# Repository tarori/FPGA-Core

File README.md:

# FPGA Core Board

* Artix-7 XC7A35T-2FTG256C
* USB Bus Powered
* 80 I/O from Mezzanine Connectors
* On-Board JTAG and 300Mbps FIFO by FT2232H
* 256Mbit Hyper-RAM

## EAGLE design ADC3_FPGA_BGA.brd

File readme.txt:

All vias with 0.3mm drill diameter should be filled and capped.

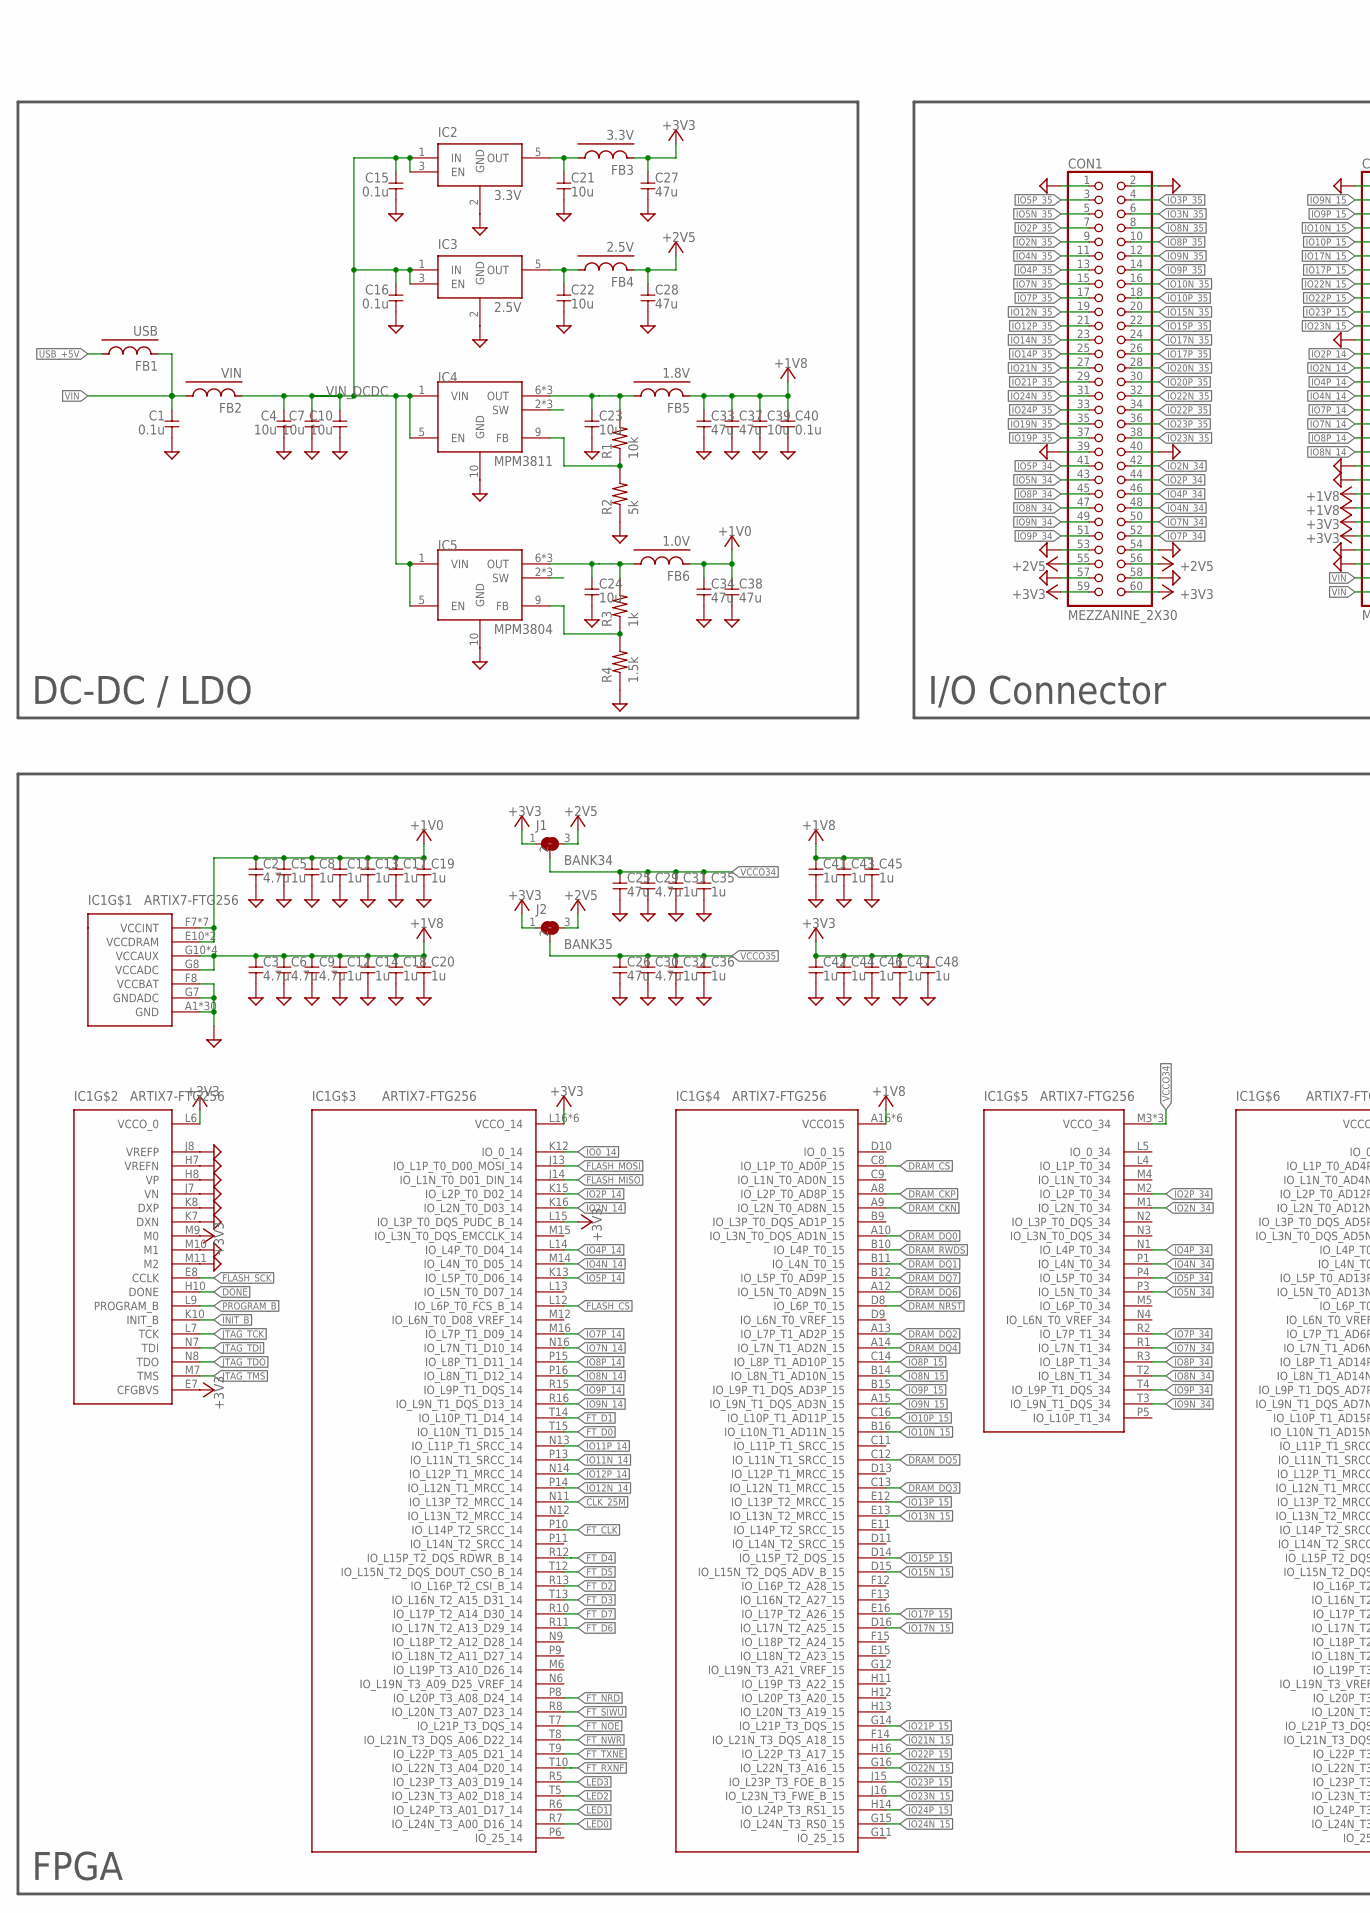
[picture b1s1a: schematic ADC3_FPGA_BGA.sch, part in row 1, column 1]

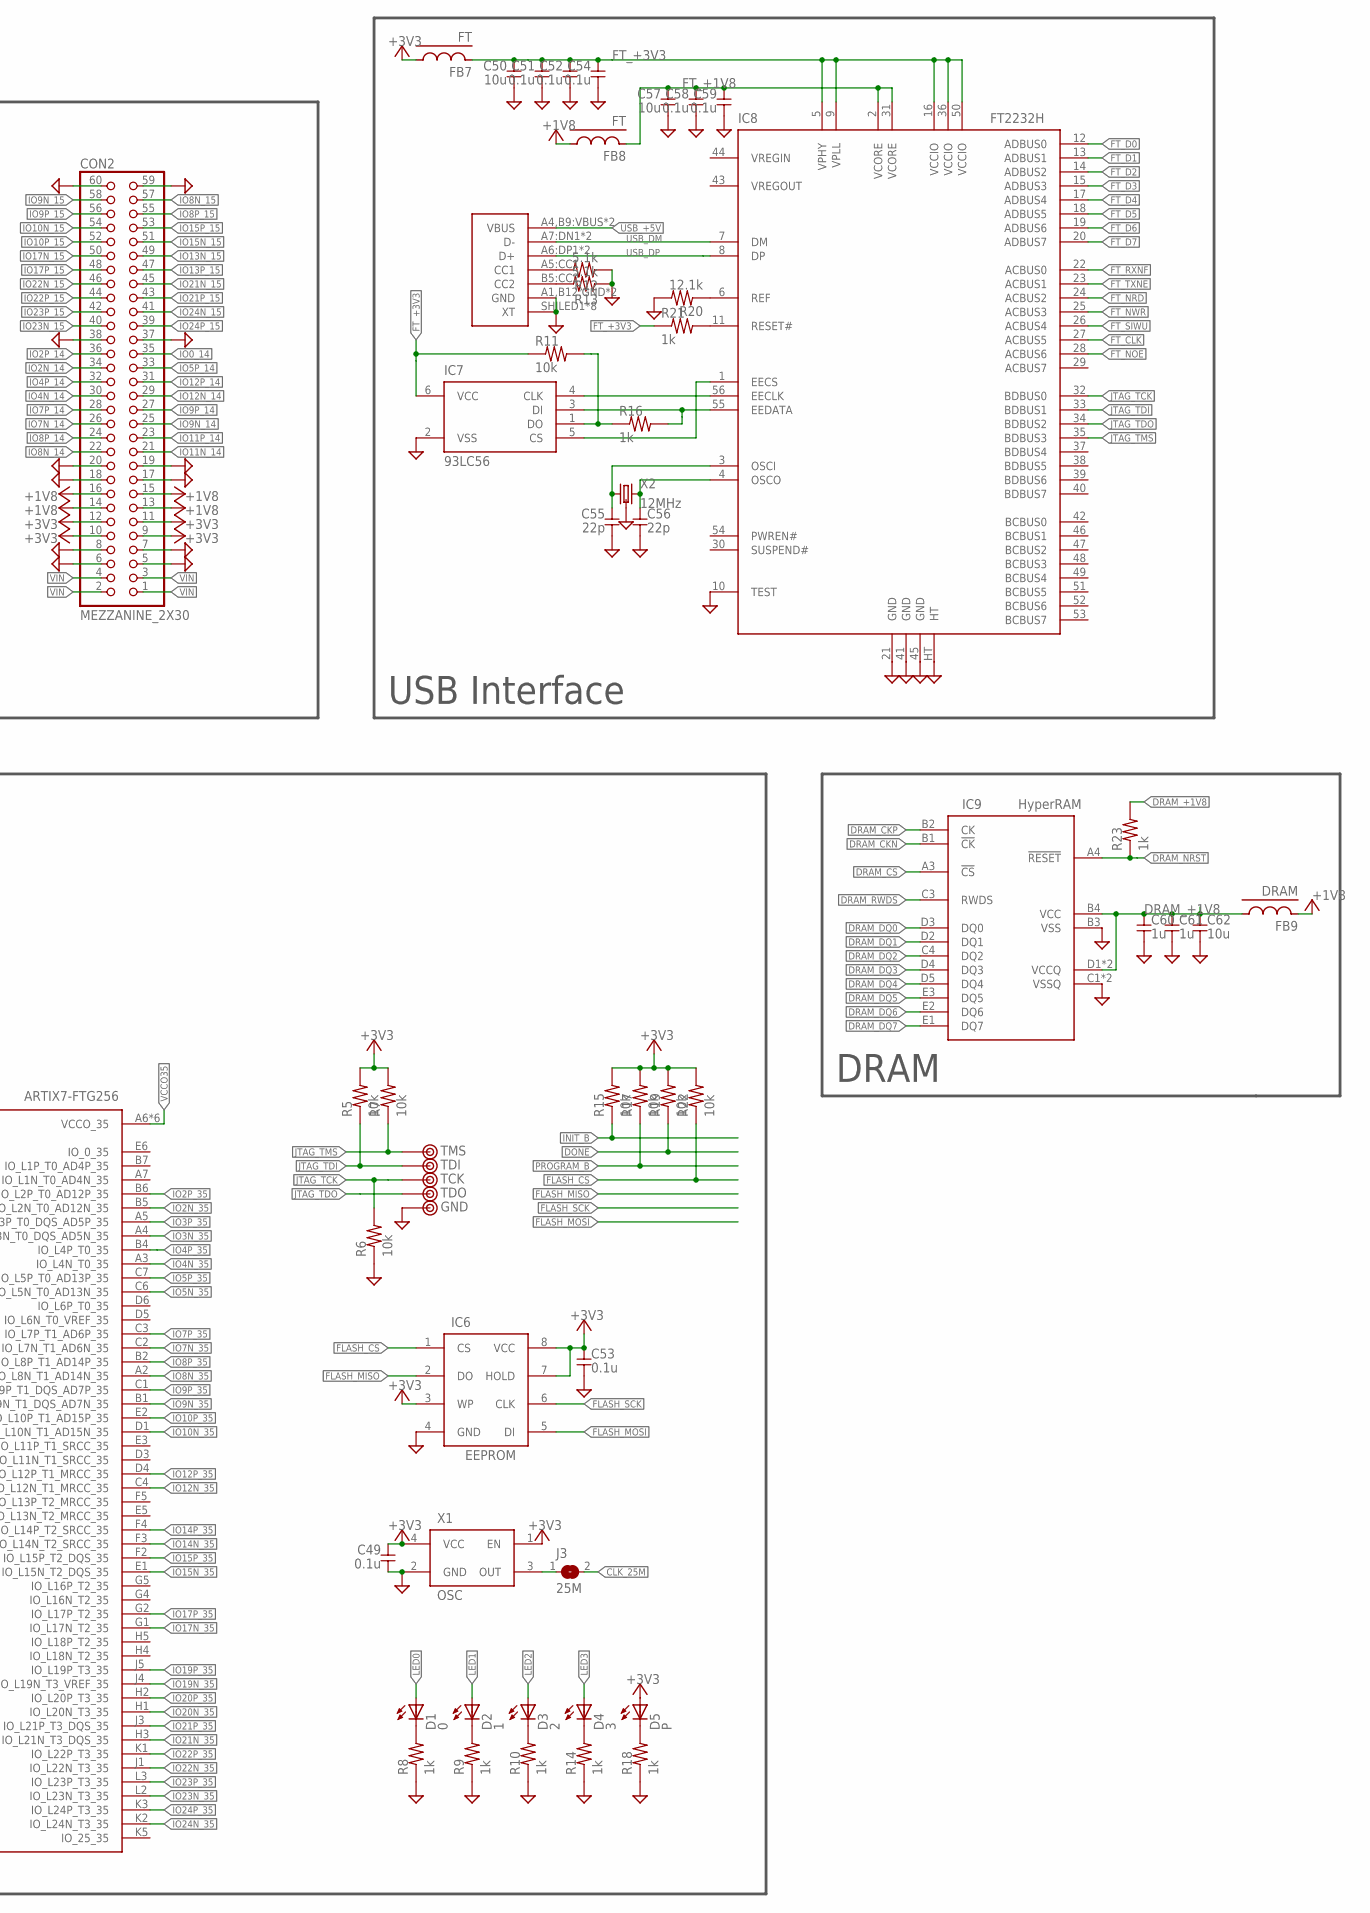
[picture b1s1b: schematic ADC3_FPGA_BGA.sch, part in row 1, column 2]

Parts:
C1, C15, C16, C40, C49, C51, C52, C53, C54, C58, C59: 0.1u; 1608C
C2, C3, C6, C9, C29, C30: 4.7u; 1608C
C4, C62: 10u; 2012
C5, C8, C11, C12, C13, C14, C17, C18, C19, C20, C31, C32, C35, C36, C41, C42, C43, C44, C45, C46, C47, C48: 1u; 1005
C7, C10, C21, C22, C23, C24, C50, C57: 10u; 1608C
C25, C26, C27, C28, C33, C34, C37, C38: 47u; 2012
C39: 10u; 3216
C55, C56: 22p; 1608C
C60, C61: 1u; 1608C
CON1, CON2: MEZZANINE_2X30; MEZZANINE_0.8MM_2X30
CON3: USB-C; 5077CR-16-SMC2-BK-TR
D1: 0; D1608
D2: 1; D1608
D3: 2; D1608
D4: 3; D1608
D5: P; D1608
FB1: USB; 1608-J
FB2: VIN; 1608-J
FB3: 3.3V; 1608-J
FB4: 2.5V; 1608-J
FB5: 1.8V; 1608-J
FB6: 1.0V; 1608-J
FB7, FB8: FT; 1608-J
FB9: DRAM; 1608-J
IC1: ARTIX7-FTG256; FTG256
IC2: 3.3V; SOT23-5
IC3: 2.5V; SOT23-5
IC4: MPM3811; QFN-10
IC5: MPM3804; QFN-10
IC6: EEPROM; SOIC-SOIJ-8
IC7: 93LC56; SOT23-6
IC8: FT2232H; QFN56-HT
IC9: HyperRAM; TFBGA24
J1: BANK34; 1608-3-J
J2: BANK35; 1608-3-J
J3: 25M; 1608-J
R1, R5, R6, R7, R11, R15, R17, R19, R22: 10k; 1608
R2: 5k; 1608
R3, R8, R9, R10, R14, R16, R18, R21, R23: 1k; 1608
R4: 1.5k; 1608
R12, R13: 5.1k; 1608
R20: 12.1k; 1608
TP1: TMS; TESTPAD-SMALL
TP2: TDI; TESTPAD-SMALL
TP3: TCK; TESTPAD-SMALL
TP4: TDO; TESTPAD-SMALL
TP5: GND; TESTPAD-SMALL
X1: OSC; KC3225
X2: 12MHz; KC3225

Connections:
1.0V_DCDC_SW: IC5.2 (SW), IC5.3 (SW), IC5.4 (SW)
1.8V_DCDC_SW: IC4.2 (SW), IC4.3 (SW), IC4.4 (SW)
+1V0: C2.1, C5.1, C8.1, C11.1, C13.1, C17.1, C19.1, C34.1, C38.1, FB6.2, IC1.E10 (VCCDRAM), IC1.F7 (VCCINT), IC1.F9 (VCCINT), IC1.F11 (VCCDRAM), IC1.G6 (VCCINT), IC1.H9 (VCCINT), IC1.J6 (VCCINT), IC1.K9 (VCCINT), IC1.L8 (VCCINT)
+1V0_DCDC: C24.1, FB6.1, IC5.6 (OUT), IC5.7 (OUT), IC5.8 (OUT), R3.2
+1V0_DCDC_FB: IC5.9 (FB), R3.1, R4.2
+1V8: C3.1, C6.1, C9.1, C12.1, C14.1, C18.1, C20.1, C33.1, C37.1, C39.1, C40.1, C41.1, C43.1, C45.1, CON2.13, CON2.14, CON2.15, CON2.16, FB5.2, FB8.1, FB9.2, IC1.A16 (VCCO15), IC1.B13 (VCCO15), IC1.C10 (VCCO15), IC1.E14 (VCCO15), IC1.G8 (VCCADC), IC1.G10 (VCCAUX), IC1.H15 (VCCO15), IC1.J10 (VCCAUX), IC1.J12 (VCCO15), IC1.K11 (VCCAUX), IC1.L10 (VCCAUX)
+1V8_DCDC: C23.1, FB5.1, IC4.6 (OUT), IC4.7 (OUT), IC4.8 (OUT), R1.2
+1V8_DCDC_FB: IC4.9 (FB), R1.1, R2.2
+2V5: C28.1, CON1.55, CON1.56, FB4.2, J1.3, J2.3
+2V5_LDO: C22.1, FB4.1, IC3.5 (OUT)
+3V3: C27.1, C42.1, C44.1, C46.1, C47.1, C48.1, C49.1, C53.1, CON1.59, CON1.60, CON2.9, CON2.10, CON2.11, CON2.12, D5.A, FB3.2, FB7.1, IC1.E7 (CFGBVS), IC1.L6 (VCCO_0), IC1.L15 (IO_L3P_T0_DQS_PUDC_B_14), IC1.L16 (VCCO_14), IC1.M9 (M0), IC1.M13 (VCCO_14), IC1.N10 (VCCO_14), IC1.P7 (VCCO_14), IC1.R14 (VCCO_14), IC1.T11 (VCCO_14), IC6.3 (WP), IC6.7 (HOLD), IC6.8 (VCC), J1.1, J2.1, R5.2, R7.2, R15.2, R17.2, R19.2, R22.2, X1.1 (EN), X1.4 (VCC)
+3V3_LDO: C21.1, FB3.1, IC2.5 (OUT)
CLK_25M: IC1.N11 (IO_L13P_T2_MRCC_14), J3.2
DONE: IC1.H10 (DONE), R19.1
DRAM_+1V8: C60.1, C61.1, C62.1, FB9.1, IC9.B4 (VCC), IC9.D1 (VCCQ), IC9.E4 (VCCQ), R23.2
DRAM_CKN: IC1.A9 (IO_L2N_T0_AD8N_15), IC9.B1 (!CK)
DRAM_CKP: IC1.A8 (IO_L2P_T0_AD8P_15), IC9.B2 (CK)
DRAM_CS: IC1.C8 (IO_L1P_T0_AD0P_15), IC9.A3 (!CS)
DRAM_DQ0: IC1.A10 (IO_L3N_T0_DQS_AD1N_15), IC9.D3 (DQ0)
DRAM_DQ1: IC1.B11 (IO_L4N_T0_15), IC9.D2 (DQ1)
DRAM_DQ2: IC1.A13 (IO_L7P_T1_AD2P_15), IC9.C4 (DQ2)
DRAM_DQ3: IC1.C13 (IO_L12N_T1_MRCC_15), IC9.D4 (DQ3)
DRAM_DQ4: IC1.A14 (IO_L7N_T1_AD2N_15), IC9.D5 (DQ4)
DRAM_DQ5: IC1.C12 (IO_L11N_T1_SRCC_15), IC9.E3 (DQ5)
DRAM_DQ6: IC1.A12 (IO_L5N_T0_AD9N_15), IC9.E2 (DQ6)
DRAM_DQ7: IC1.B12 (IO_L5P_T0_AD9P_15), IC9.E1 (DQ7)
DRAM_NRST: IC1.D8 (IO_L6P_T0_15), IC9.A4 (!RESET), R23.1
DRAM_RWDS: IC1.B10 (IO_L4P_T0_15), IC9.C3 (RWDS)
FLASH_CS: IC1.L12 (IO_L6P_T0_FCS_B_14), IC6.1 (CS), R22.1
FLASH_MISO: IC1.J14 (IO_L1N_T0_D01_DIN_14), IC6.2 (DO)
FLASH_MOSI: IC1.J13 (IO_L1P_T0_D00_MOSI_14), IC6.5 (DI)
FLASH_SCK: IC1.E8 (CCLK), IC6.6 (CLK)
FT_+1V8: C57.1, C58.1, C59.1, FB8.2, IC8.2 (VCORE), IC8.31 (VCORE)
FT_+3V3: C50.1, C51.1, C52.1, C54.1, FB7.2, IC7.6 (VCC), IC8.5 (VPHY), IC8.9 (VPLL), IC8.16 (VCCIO), IC8.36 (VCCIO), IC8.50 (VCCIO), R11.1, R21.1
FT_CLK: IC1.P10 (IO_L14P_T2_SRCC_14), IC8.27 (ACBUS5)
FT_D0: IC1.T15 (IO_L10N_T1_D15_14), IC8.12 (ADBUS0)
FT_D1: IC1.T14 (IO_L10P_T1_D14_14), IC8.13 (ADBUS1)
FT_D2: IC1.R13 (IO_L16P_T2_CSI_B_14), IC8.14 (ADBUS2)
FT_D3: IC1.T13 (IO_L16N_T2_A15_D31_14), IC8.15 (ADBUS3)
FT_D4: IC1.R12 (IO_L15P_T2_DQS_RDWR_B_14), IC8.17 (ADBUS4)
FT_D5: IC1.T12 (IO_L15N_T2_DQS_DOUT_CSO_B_14), IC8.18 (ADBUS5)
FT_D6: IC1.R11 (IO_L17N_T2_A13_D29_14), IC8.19 (ADBUS6)
FT_D7: IC1.R10 (IO_L17P_T2_A14_D30_14), IC8.20 (ADBUS7)
FT_NOE: IC1.T7 (IO_L21P_T3_DQS_14), IC8.28 (ACBUS6)
FT_NRD: IC1.P8 (IO_L20P_T3_A08_D24_14), IC8.24 (ACBUS2)
FT_NWR: IC1.T8 (IO_L21N_T3_DQS_A06_D22_14), IC8.25 (ACBUS3)
FT_RXNF: IC1.T10 (IO_L22N_T3_A04_D20_14), IC8.22 (ACBUS0)
FT_SIWU: IC1.R8 (IO_L20N_T3_A07_D23_14), IC8.26 (ACBUS4)
FT_TXNE: IC1.T9 (IO_L22P_T3_A05_D21_14), IC8.23 (ACBUS1)
GND: C1.2, C2.2, C3.2, C4.2, C5.2, C6.2, C7.2, C8.2, C9.2, C10.2, C11.2, C12.2, C13.2, C14.2, C15.2, C16.2, C17.2, C18.2, C19.2, C20.2, C21.2, C22.2, C23.2, C24.2, C25.2, C26.2, C27.2, C28.2, C29.2, C30.2, C31.2, C32.2, C33.2, C34.2, C35.2, C36.2, C37.2, C38.2, C39.2, C40.2, C41.2, C42.2, C43.2, C44.2, C45.2, C46.2, C47.2, C48.2, C49.2, C50.2, C51.2, C52.2, C53.2, C54.2, C55.2, C56.2, C57.2, C58.2, C59.2, C60.2, C61.2, C62.2, CON1.1, CON1.2, CON1.39, CON1.40, CON1.53, CON1.54, CON1.57, CON1.58, CON2.5, CON2.6, CON2.7, CON2.8, CON2.17, CON2.18, CON2.19, CON2.20, CON2.37, CON2.38, CON2.59, CON2.60, CON3.A1,B12:GND (GND), CON3.B1,A12:GND (GND), CON3.SHILED1 (XT), CON3.SHILED2 (XT), CON3.SHILED3 (XT), CON3.SHILED4 (XT), CON3.SHILED5 (XT), CON3.SHILED6 (XT), CON3.SHILED7 (XT), CON3.SHILED8 (XT), IC1.A1 (GND), IC1.A11 (GND), IC1.B8 (GND), IC1.C5 (GND), IC1.C15 (GND), IC1.D2 (GND), IC1.D12 (GND), IC1.E9 (GND), IC1.F6 (GND), IC1.F8 (VCCBAT), IC1.F10 (GND), IC1.F16 (GND), IC1.G3 (GND), IC1.G7 (GNDADC), IC1.G9 (GND), IC1.G13 (GND), IC1.H6 (GND), IC1.H7 (VREFN), IC1.H8 (VP), IC1.J7 (VN), IC1.J8 (VREFP), IC1.J9 (GND), IC1.J11 (GND), IC1.K4 (GND), IC1.K6 (GND), IC1.K7 (DXN), IC1.K8 (DXP), IC1.K14 (GND), IC1.L1 (GND), IC1.L11 (GND), IC1.M8 (GND), IC1.M10 (M1), IC1.M11 (M2), IC1.N5 (GND), IC1.N15 (GND), IC1.P2 (GND), IC1.P12 (GND), IC1.R9 (GND), IC1.T6 (GND), IC1.T16 (GND), IC2.2 (GND), IC3.2 (GND), IC4.10 (GND), IC5.10 (GND), IC6.4 (GND), IC7.2 (VSS), IC8.10 (TEST), IC8.21 (GND), IC8.41 (GND), IC8.45 (GND), IC8.HT, IC9.B3 (VSS), IC9.C1 (VSSQ), IC9.E5 (VSSQ), R2.1, R4.1, R6.1, R8.1, R9.1, R10.1, R12.1, R13.1, R14.1, R18.1, R20.2, TP5.1, X1.2 (GND), X2.2 (GND), X2.4 (GND)
INIT_B: IC1.K10 (INIT_B), R15.1
IO0_14: CON2.35, IC1.K12 (IO_0_14)
IO2N_14: CON2.34, IC1.K16 (IO_L2N_T0_D03_14)
IO2N_34: CON1.42, IC1.M1 (IO_L2N_T0_34)
IO2N_35: CON1.9, IC1.B5 (IO_L2N_T0_AD12N_35)
IO2P_14: CON2.36, IC1.K15 (IO_L2P_T0_D02_14)
IO2P_34: CON1.44, IC1.M2 (IO_L2P_T0_34)
IO2P_35: CON1.7, IC1.B6 (IO_L2P_T0_AD12P_35)
IO3N_35: CON1.6, IC1.A4 (IO_L3N_T0_DQS_AD5N_35)
IO3P_35: CON1.4, IC1.A5 (IO_L3P_T0_DQS_AD5P_35)
IO4N_14: CON2.30, IC1.M14 (IO_L4N_T0_D05_14)
IO4N_34: CON1.48, IC1.P1 (IO_L4N_T0_34)
IO4N_35: CON1.11, IC1.A3 (IO_L4N_T0_35)
IO4P_14: CON2.32, IC1.L14 (IO_L4P_T0_D04_14)
IO4P_34: CON1.46, IC1.N1 (IO_L4P_T0_34)
IO4P_35: CON1.13, IC1.B4 (IO_L4P_T0_35)
IO5N_34: CON1.43, IC1.P3 (IO_L5N_T0_34)
IO5N_35: CON1.5, IC1.C6 (IO_L5N_T0_AD13N_35)
IO5P_14: CON2.33, IC1.K13 (IO_L5P_T0_D06_14)
IO5P_34: CON1.41, IC1.P4 (IO_L5P_T0_34)
IO5P_35: CON1.3, IC1.C7 (IO_L5P_T0_AD13P_35)
IO7N_14: CON2.26, IC1.N16 (IO_L7N_T1_D10_14)
IO7N_34: CON1.50, IC1.R1 (IO_L7N_T1_34)
IO7N_35: CON1.15, IC1.C2 (IO_L7N_T1_AD6N_35)
IO7P_14: CON2.28, IC1.M16 (IO_L7P_T1_D09_14)
IO7P_34: CON1.52, IC1.R2 (IO_L7P_T1_34)
IO7P_35: CON1.17, IC1.C3 (IO_L7P_T1_AD6P_35)
IO8N_14: CON2.22, IC1.P16 (IO_L8N_T1_D12_14)
IO8N_15: CON2.57, IC1.B14 (IO_L8N_T1_AD10N_15)
IO8N_34: CON1.47, IC1.T2 (IO_L8N_T1_34)
IO8N_35: CON1.8, IC1.A2 (IO_L8N_T1_AD14N_35)
IO8P_14: CON2.24, IC1.P15 (IO_L8P_T1_D11_14)
IO8P_15: CON2.55, IC1.C14 (IO_L8P_T1_AD10P_15)
IO8P_34: CON1.45, IC1.R3 (IO_L8P_T1_34)
IO8P_35: CON1.10, IC1.B2 (IO_L8P_T1_AD14P_35)
IO9N_14: CON2.25, IC1.R16 (IO_L9N_T1_DQS_D13_14)
IO9N_15: CON2.58, IC1.A15 (IO_L9N_T1_DQS_AD3N_15)
IO9N_34: CON1.49, IC1.T3 (IO_L9N_T1_DQS_34)
IO9N_35: CON1.12, IC1.B1 (IO_L9N_T1_DQS_AD7N_35)
IO9P_14: CON2.27, IC1.R15 (IO_L9P_T1_DQS_14)
IO9P_15: CON2.56, IC1.B15 (IO_L9P_T1_DQS_AD3P_15)
IO9P_34: CON1.51, IC1.T4 (IO_L9P_T1_DQS_34)
IO9P_35: CON1.14, IC1.C1 (IO_L9P_T1_DQS_AD7P_35)
IO10N_15: CON2.54, IC1.B16 (IO_L10N_T1_AD11N_15)
IO10N_35: CON1.16, IC1.D1 (IO_L10N_T1_AD15N_35)
IO10P_15: CON2.52, IC1.C16 (IO_L10P_T1_AD11P_15)
IO10P_35: CON1.18, IC1.E2 (IO_L10P_T1_AD15P_35)
IO11N_14: CON2.21, IC1.P13 (IO_L11N_T1_SRCC_14)
IO11P_14: CON2.23, IC1.N13 (IO_L11P_T1_SRCC_14)
IO12N_14: CON2.29, IC1.P14 (IO_L12N_T1_MRCC_14)
IO12N_35: CON1.19, IC1.C4 (IO_L12N_T1_MRCC_35)
IO12P_14: CON2.31, IC1.N14 (IO_L12P_T1_MRCC_14)
IO12P_35: CON1.21, IC1.D4 (IO_L12P_T1_MRCC_35)
IO13N_15: CON2.49, IC1.E13 (IO_L13N_T2_MRCC_15)
IO13P_15: CON2.47, IC1.E12 (IO_L13P_T2_MRCC_15)
IO14N_35: CON1.23, IC1.F3 (IO_L14N_T2_SRCC_35)
IO14P_35: CON1.25, IC1.F4 (IO_L14P_T2_SRCC_35)
IO15N_15: CON2.51, IC1.D15 (IO_L15N_T2_DQS_ADV_B_15)
IO15N_35: CON1.20, IC1.E1 (IO_L15N_T2_DQS_35)
IO15P_15: CON2.53, IC1.D14 (IO_L15P_T2_DQS_15)
IO15P_35: CON1.22, IC1.F2 (IO_L15P_T2_DQS_35)
IO17N_15: CON2.50, IC1.D16 (IO_L17N_T2_A25_15)
IO17N_35: CON1.24, IC1.G1 (IO_L17N_T2_35)
IO17P_15: CON2.48, IC1.E16 (IO_L17P_T2_A26_15)
IO17P_35: CON1.26, IC1.G2 (IO_L17P_T2_35)
IO19N_35: CON1.35, IC1.J4 (IO_L19N_T3_VREF_35)
IO19P_35: CON1.37, IC1.J5 (IO_L19P_T3_35)
IO20N_35: CON1.28, IC1.H1 (IO_L20N_T3_35)
IO20P_35: CON1.30, IC1.H2 (IO_L20P_T3_35)
IO21N_15: CON2.45, IC1.F14 (IO_L21N_T3_DQS_A18_15)
IO21N_35: CON1.27, IC1.H3 (IO_L21N_T3_DQS_35)
IO21P_15: CON2.43, IC1.G14 (IO_L21P_T3_DQS_15)
IO21P_35: CON1.29, IC1.J3 (IO_L21P_T3_DQS_35)
IO22N_15: CON2.46, IC1.G16 (IO_L22N_T3_A16_15)
IO22N_35: CON1.32, IC1.J1 (IO_L22N_T3_35)
IO22P_15: CON2.44, IC1.H16 (IO_L22P_T3_A17_15)
IO22P_35: CON1.34, IC1.K1 (IO_L22P_T3_35)
IO23N_15: CON2.40, IC1.J16 (IO_L23N_T3_FWE_B_15)
IO23N_35: CON1.38, IC1.L2 (IO_L23N_T3_35)
IO23P_15: CON2.42, IC1.J15 (IO_L23P_T3_FOE_B_15)
IO23P_35: CON1.36, IC1.L3 (IO_L23P_T3_35)
IO24N_15: CON2.41, IC1.G15 (IO_L24N_T3_RS0_15)
IO24N_35: CON1.31, IC1.K2 (IO_L24N_T3_35)
IO24P_15: CON2.39, IC1.H14 (IO_L24P_T3_RS1_15)
IO24P_35: CON1.33, IC1.K3 (IO_L24P_T3_35)
JTAG_TCK: IC1.L7 (TCK), IC8.32 (BDBUS0), R6.2, TP3.1
JTAG_TDI: IC1.N7 (TDI), IC8.33 (BDBUS1), R5.1, TP2.1
JTAG_TDO: IC1.N8 (TDO), IC8.34 (BDBUS2), TP4.1
JTAG_TMS: IC1.M7 (TMS), IC8.35 (BDBUS3), R7.1, TP1.1
LED0: D1.A, IC1.R7 (IO_L24N_T3_A00_D16_14)
LED1: D2.A, IC1.R6 (IO_L24P_T3_A01_D17_14)
LED2: D3.A, IC1.T5 (IO_L23N_T3_A02_D18_14)
LED3: D4.A, IC1.R5 (IO_L23P_T3_A03_D19_14)
unnamed: D5.K, R18.2
unnamed: D1.K, R8.2
unnamed: D2.K, R9.2
unnamed: D3.K, R10.2
unnamed: D4.K, R14.2
unnamed: CON3.A5:CC1 (CC1), R12.2
unnamed: CON3.B5:CC2 (CC2), R13.2
unnamed: J3.1, X1.3 (OUT)
unnamed: IC7.4 (CLK), IC8.56 (EECLK)
unnamed: IC7.3 (DI), IC8.55 (EEDATA), R16.2
unnamed: IC7.5 (CS), IC8.1 (EECS)
unnamed: IC7.1 (DO), R11.2, R16.1
unnamed: C56.1, IC8.4 (OSCO), X2.3 (2)
unnamed: C55.1, IC8.3 (OSCI), X2.1
unnamed: IC8.6 (REF), R20.1
unnamed: IC8.11 (RESET#), R21.2
PROGRAM_B: IC1.L9 (PROGRAM_B), R17.1
USB_+5V: CON3.A4,B9:VBUS (VBUS), CON3.B4,A9:VBUS (VBUS), FB1.1
USB_DM: CON3.A7:DN1 (D-), CON3.B7:DN2 (D-), IC8.7 (DM)
USB_DP: CON3.A6:DP1 (D+), CON3.B6:DP2 (D+), IC8.8 (DP)
VCCO34: C25.1, C29.1, C31.1, C35.1, IC1.M3 (VCCO_34), IC1.R4 (VCCO_34), IC1.T1 (VCCO_34), J1.2
VCCO35: C26.1, C30.1, C32.1, C36.1, IC1.A6 (VCCO_35), IC1.B3 (VCCO_35), IC1.D7 (VCCO_35), IC1.E4 (VCCO_35), IC1.F1 (VCCO_35), IC1.J2 (VCCO_35), J2.2
VIN: C1.1, CON2.1, CON2.2, CON2.3, CON2.4, FB1.2, FB2.1
VIN_DCDC: C4.1, C7.1, C10.1, C15.1, C16.1, FB2.2, IC2.1 (IN), IC2.3 (EN), IC3.1 (IN), IC3.3 (EN), IC4.1 (VIN), IC4.5 (EN), IC5.1 (VIN), IC5.5 (EN)

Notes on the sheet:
USB Interface
DRAM
I/O Connector
DC-DC / LDO
FPGA

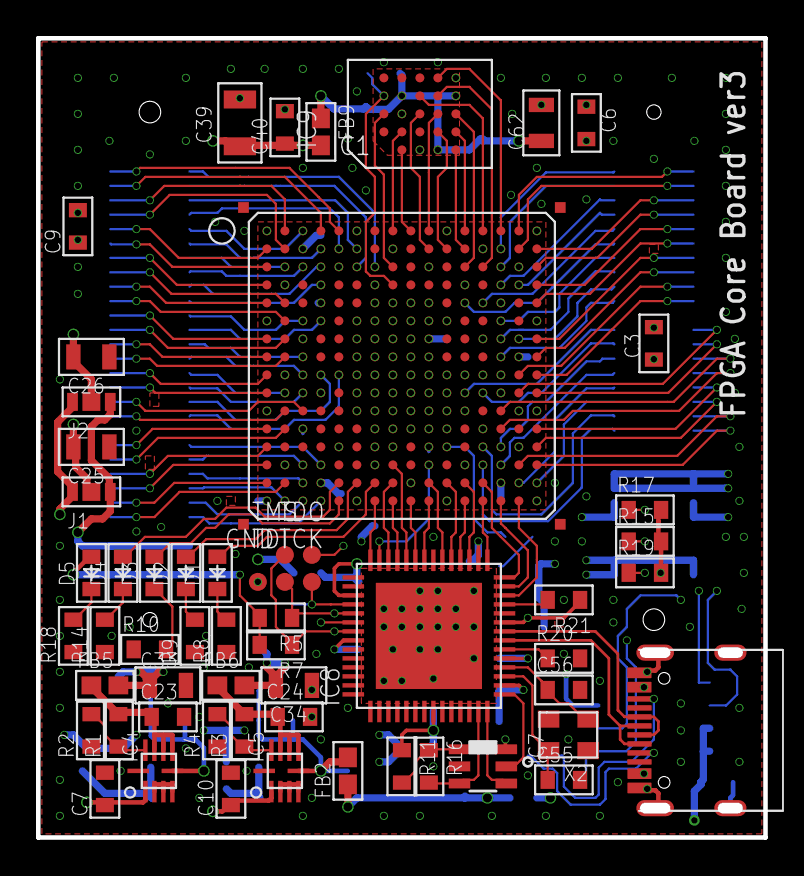
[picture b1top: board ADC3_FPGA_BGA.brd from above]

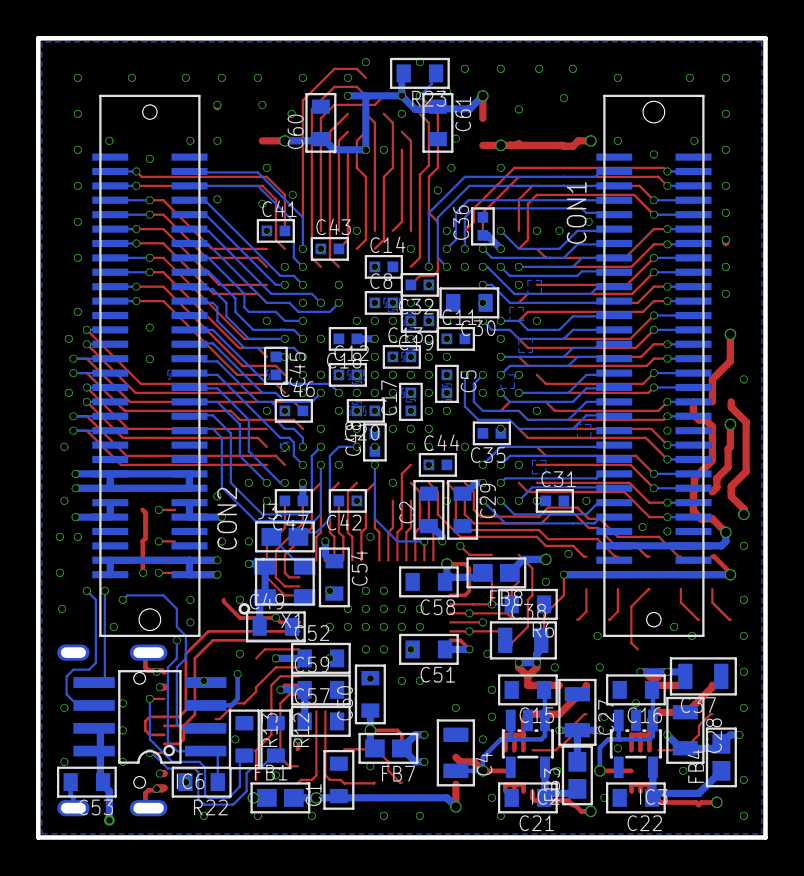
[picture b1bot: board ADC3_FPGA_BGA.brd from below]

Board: 6 copper layers, 40.4 x 44.4 mm, 121 parts (63 on the bottom side), 167 nets.

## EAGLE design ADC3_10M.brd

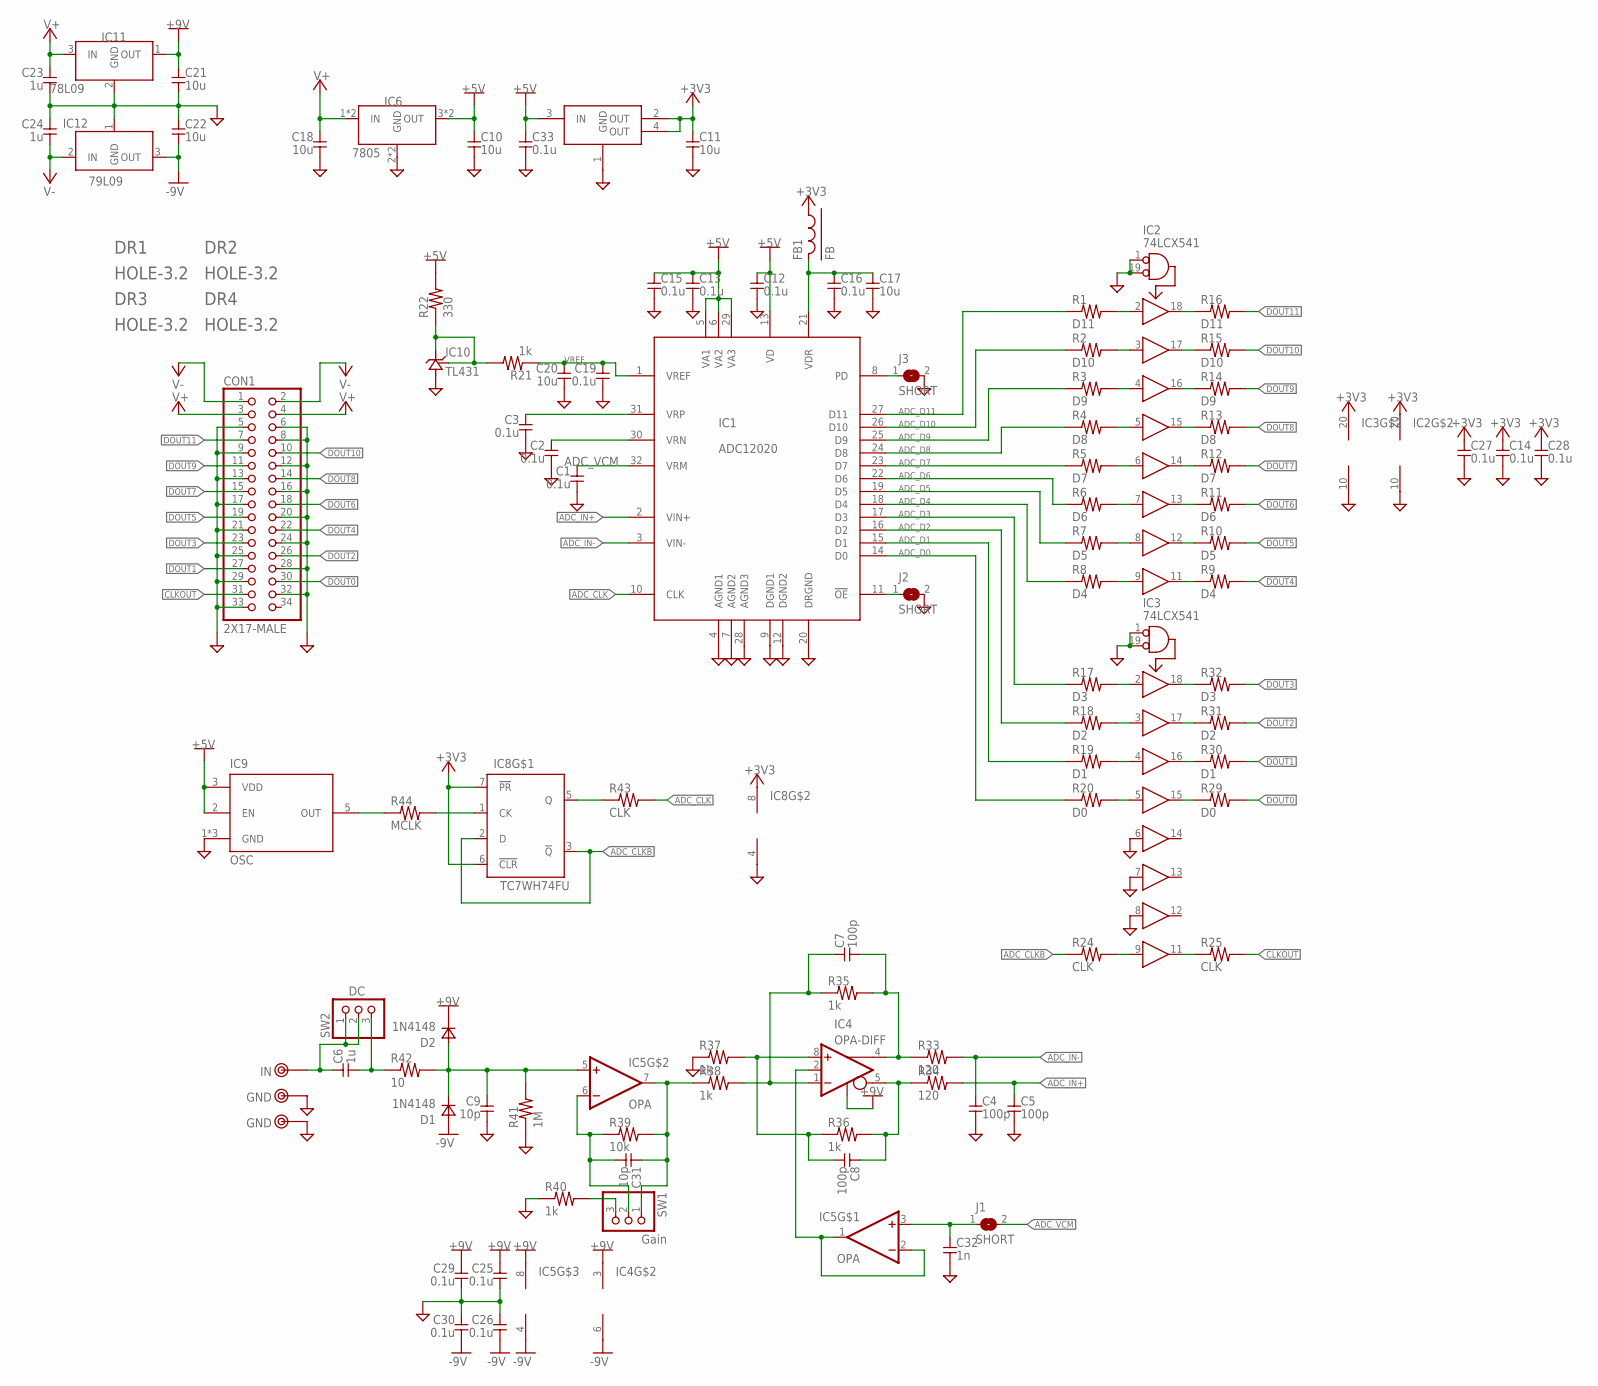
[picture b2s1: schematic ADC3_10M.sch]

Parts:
C1, C2, C3, C12, C13, C14, C15, C16, C19, C25, C26, C27, C28, C29, C30, C33: 0.1u; 1608
C4, C5, C7, C8: 100p; 1608
C6: 1u; C050
C9, C31: 10p; 1608
C10, C11, C18, C20: 10u; 3216
C17, C21, C22: 10u; 2012
C23, C24: 1u; 1608
C32: 1n; 1608
CON1: 2X17-MALE; 2X17/90-SWAPPED
D1, D2: 1N4148; SOD123
DR1, DR2, DR3, DR4: HOLE-3.2; HOLE_3.2
FB1: FB; 1608-J
IC1: ADC12020; TQFP32-08
IC2, IC3: 74LCX541; TSSOP20
IC4: OPA-DIFF; SOP8
IC5: OPA; SOP8
IC6: 7805; TO220-SOP-DUAL
IC7: AZ1086H-3.3; SOT223
IC8: TC7WH74FU; SSOP8-P-0.65
IC9: OSC; MY_OSC
IC10: TL431; TO-92
IC11: 78L09; TO-92
IC12: 79L09; TO-92
J1, J2, J3: SHORT; 1608-J
R1, R16: D11; 1608-J
R2, R15: D10; 1608-J
R3, R14: D9; 1608-J
R4, R13: D8; 1608-J
R5, R12: D7; 1608-J
R6, R11: D6; 1608-J
R7, R10: D5; 1608-J
R8, R9: D4; 1608-J
R17, R32: D3; 1608-J
R18, R31: D2; 1608-J
R19, R30: D1; 1608-J
R20, R29: D0; 1608-J
R21, R35, R36, R37, R38, R40: 1k; 1608
R22: 330; 1608
R24, R25, R43: CLK; 1608-J
R33, R34: 120; 1608
R39: 10k; 1608
R41: 1M; 1608
R42: 10; 1608
R44: MCLK; 1608-J
SW1: Gain; 1X03
SW2: DC; 1X03
TP1: IN; TESTPIN
TP2, TP3: GND; TESTPIN

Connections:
+3V3: C11.1, C14.1, C27.1, C28.1, FB1.1, IC2.20 (V+), IC3.20 (V+), IC7.2 (OUT), IC7.4 (OUT), IC8.6 (!CLR), IC8.7 (!PR), IC8.8 (V+)
+5V: C10.1, C12.1, C13.1, C15.1, C33.1, IC1.5 (VA1), IC1.6 (VA2), IC1.13 (VD), IC1.29 (VA3), IC6.3 (OUT), IC6.6 (OUT), IC7.3 (IN), IC9.2 (EN), IC9.3 (VDD), R22.2
+9V: C21.1, C25.1, C29.1, D2.2 (K), IC4.3 (V+), IC4.7 (EN), IC5.8 (V+), IC11.1 (OUT)
-9V: C22.2, C26.2, C30.2, D1.1 (A), IC4.6 (V-), IC5.4 (V-), IC12.3 (OUT)
ADC_CLK: IC1.10 (CLK), R43.2
ADC_CLKB: IC8.2 (D), IC8.3 (!Q), R24.1
ADC_D0: IC1.14 (D0), R20.1
ADC_D1: IC1.15 (D1), R19.1
ADC_D2: IC1.16 (D2), R18.1
ADC_D3: IC1.17 (D3), R17.1
ADC_D4: IC1.18 (D4), R8.1
ADC_D5: IC1.19 (D5), R7.1
ADC_D6: IC1.22 (D6), R6.1
ADC_D7: IC1.23 (D7), R5.1
ADC_D8: IC1.24 (D8), R4.1
ADC_D9: IC1.25 (D9), R3.1
ADC_D10: IC1.26 (D10), R2.1
ADC_D11: IC1.27 (D11), R1.1
ADC_IN+: C5.1, IC1.2 (VIN+), R34.2
ADC_IN-: C4.1, IC1.3 (VIN-), R33.2
ADC_VCM: C1.1, IC1.32 (VRM), J1.2
CLKOUT: CON1.31, R25.2
DOUT0: CON1.30, R29.2
DOUT1: CON1.27, R30.2
DOUT2: CON1.26, R31.2
DOUT3: CON1.23, R32.2
DOUT4: CON1.22, R9.2
DOUT5: CON1.19, R10.2
DOUT6: CON1.18, R11.2
DOUT7: CON1.15, R12.2
DOUT8: CON1.14, R13.2
DOUT9: CON1.11, R14.2
DOUT10: CON1.10, R15.2
DOUT11: CON1.7, R16.2
GND: C1.2, C2.2, C3.2, C4.2, C5.2, C9.2, C10.2, C11.2, C12.2, C13.2, C14.2, C15.2, C16.2, C17.2, C18.2, C19.2, C20.2, C21.2, C22.1, C23.2, C24.1, C25.2, C26.1, C27.2, C28.2, C29.2, C30.1, C32.2, C33.2, CON1.5, CON1.6, CON1.8, CON1.9, CON1.12, CON1.13, CON1.16, CON1.17, CON1.20, CON1.21, CON1.24, CON1.25, CON1.28, CON1.29, CON1.32, CON1.33, IC1.4 (AGND1), IC1.7 (AGND2), IC1.9 (DGND1), IC1.12 (DGND2), IC1.20 (DRGND), IC1.28 (AGND3), IC2.1 (!OE1), IC2.10 (V-), IC2.19 (!OE2), IC3.1 (!OE1), IC3.6 (IN5), IC3.7 (IN6), IC3.8 (IN7), IC3.10 (V-), IC3.19 (!OE2), IC6.2 (GND), IC6.5 (GND), IC7.1 (GND), IC8.4 (V-), IC9.1 (GND), IC9.4 (GND), IC9.6 (GND), IC10.2 (GND), IC11.2 (GND), IC12.1 (GND), J2.2, J3.2, R37.1, R40.1, R41.1, TP2.1, TP3.1
unnamed: C7.2, IC4.4 (+OUT), R33.1, R35.2
unnamed: C8.1, IC4.5 (-OUT), R34.1, R36.2
unnamed: C8.2, IC4.8 (+IN), R36.1, R37.2
unnamed: R40.2, SW1.3
unnamed: C7.1, IC4.1 (-IN), R35.1, R38.2
unnamed: IC4.2 (CM), IC5.1 (OUT), IC5.2 (-IN)
unnamed: C32.1, IC5.3 (+IN), J1.1
unnamed: C31.1, IC5.7 (OUT), R38.1, R39.2, SW1.1
unnamed: C31.2, IC5.6 (-IN), R39.1, SW1.2
unnamed: IC2.2 (IN1), R1.2
unnamed: IC2.3 (IN2), R2.2
unnamed: IC2.4 (IN3), R3.2
unnamed: IC2.5 (IN4), R4.2
unnamed: IC2.6 (IN5), R5.2
unnamed: IC2.7 (IN6), R6.2
unnamed: IC2.8 (IN7), R7.2
unnamed: IC2.9 (IN8), R8.2
unnamed: IC2.11 (OUT8), R9.1
unnamed: IC2.12 (OUT7), R10.1
unnamed: IC2.13 (OUT6), R11.1
unnamed: IC2.14 (OUT5), R12.1
unnamed: IC2.15 (OUT4), R13.1
unnamed: IC2.16 (OUT3), R14.1
unnamed: IC2.17 (OUT2), R15.1
unnamed: IC2.18 (OUT1), R16.1
unnamed: C16.1, C17.1, FB1.2, IC1.21 (VDR)
unnamed: C6.1, SW2.1, SW2.2, TP1.1
unnamed: C6.2, R42.1, SW2.3
unnamed: C9.1, D1.2 (K), D2.1 (A), IC5.5 (+IN), R41.2, R42.2
unnamed: IC1.11 (!OE), J2.1
unnamed: IC1.8 (PD), J3.1
unnamed: IC10.1 (REF), IC10.3 (OUT), R21.2, R22.1
unnamed: IC3.2 (IN1), R17.2
unnamed: IC3.3 (IN2), R18.2
unnamed: IC3.4 (IN3), R19.2
unnamed: IC3.5 (IN4), R20.2
unnamed: IC3.9 (IN8), R24.2
unnamed: IC3.11 (OUT8), R25.1
unnamed: IC3.15 (OUT4), R29.1
unnamed: IC3.16 (OUT3), R30.1
unnamed: IC3.17 (OUT2), R31.1
unnamed: IC3.18 (OUT1), R32.1
unnamed: IC8.5 (Q), R43.1
unnamed: C2.1, IC1.30 (VRN)
unnamed: C3.1, IC1.31 (VRP)
unnamed: IC8.1 (CK), R44.2
unnamed: IC9.5 (OUT), R44.1
V+: C18.1, C23.1, CON1.3, CON1.4, IC6.1 (IN), IC6.4 (IN), IC11.3 (IN)
V-: C24.2, CON1.1, CON1.2, IC12.2 (IN)
VREF: C19.1, C20.1, IC1.1 (VREF), R21.1

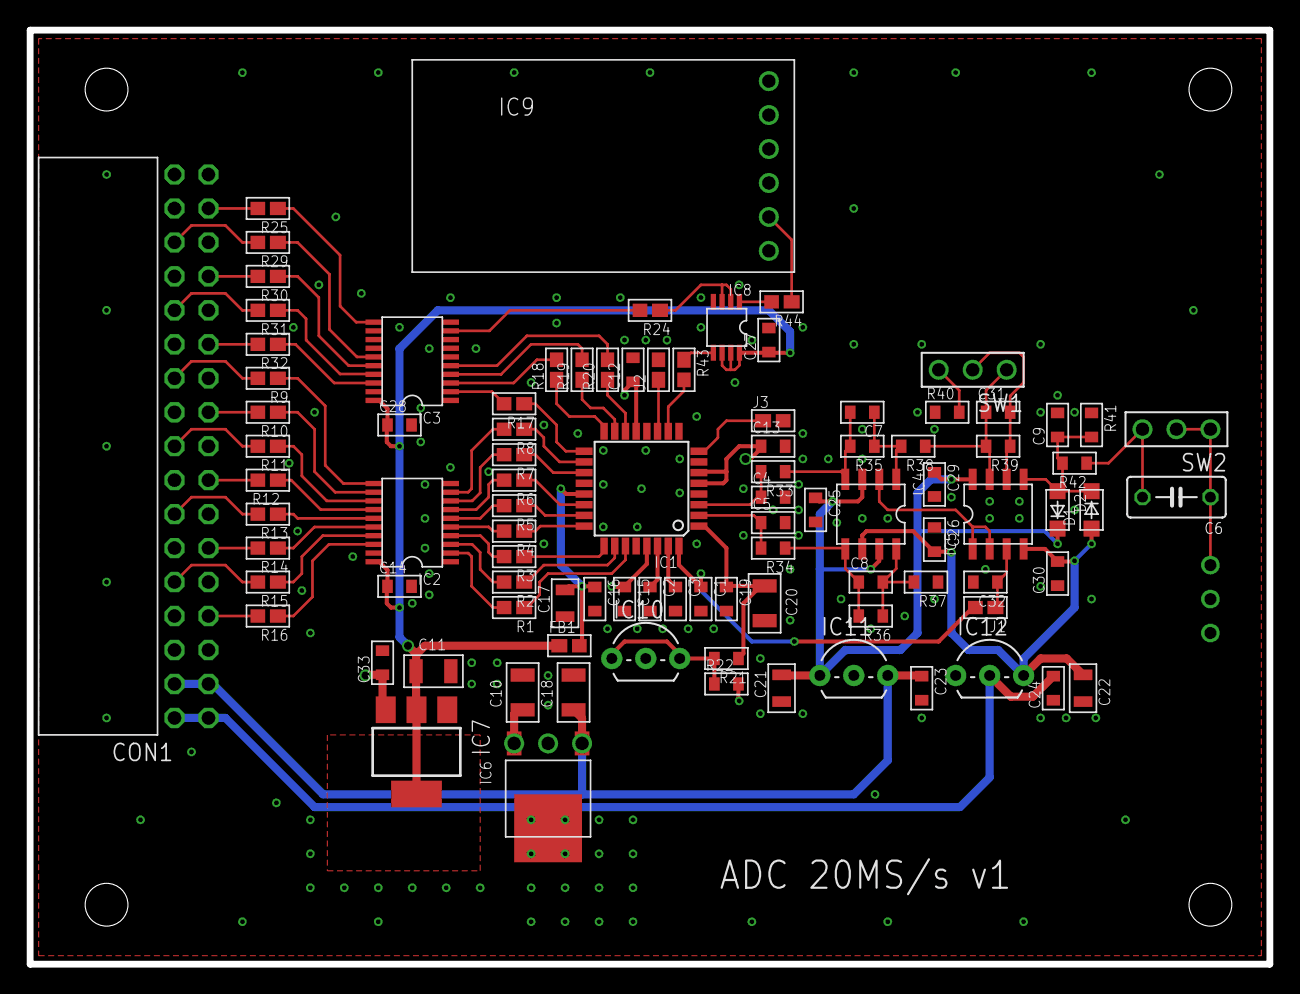
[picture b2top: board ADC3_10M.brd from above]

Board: 4 copper layers, 92.7 x 69.9 mm, 101 parts (0 on the bottom side), 85 nets.
